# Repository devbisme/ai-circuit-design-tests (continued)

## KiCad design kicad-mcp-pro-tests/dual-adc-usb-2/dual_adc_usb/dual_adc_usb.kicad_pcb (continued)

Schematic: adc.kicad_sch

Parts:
C401, C402, C403, C404, C406, C407, C409, C410, C412, C413, C416, C417: 100n; C_0603_1608Metric
C405: 10u; C_0805_2012Metric
C408, C411, C414, C415: 2.2u; C_0603_1608Metric
R401: 20k; R_0603_1608Metric
R402: 10k; R_0603_1608Metric
R403, R404, R405, R406: 33; R_0603_1608Metric
RN401, RN402, RN403, RN404, RN405, RN406: 4x33; R_Array_Convex_4x0603
U401: LTC2290CUP; QFN-64-1EP_9x9mm_P0.5mm_EP7.15x7.15mm
U402: 74LVC1G34; SOT-23-5
X401: ASE-10.000MHz; Oscillator_SMD_Abracon_ASE-4Pin_3.2x2.5mm

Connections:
+3.3VA: C401.1, C402.1, C403.1, C404.1, C405.1, C416.1, R401.1, U401.7 (VDD), U401.10 (VDD), U401.18 (VDD), U401.19 (SENSEB), U401.21 (MUX), U401.62 (SENSEA), U401.63 (VDD), X401.1 (EN), X401.4 (Vdd); also elsewhere on the board
+3V3: C406.1, C407.1, C417.1, U401.32 (OVDD), U401.49 (OVDD), U402.5 (VCC); also elsewhere on the board
/ADC/ADC_CLK: R403.2, U401.8 (CLKA), U401.9 (CLKB)
/ADC/CLK_BUF: R404.1, U402.4
/ADC/DA0_S: RN401.1 (R1.1), U401.43 (DA0)
/ADC/DA1_S: RN401.2 (R2.1), U401.44 (DA1)
/ADC/DA2_S: RN401.3 (R3.1), U401.45 (DA2)
/ADC/DA3_S: RN401.4 (R4.1), U401.46 (DA3)
/ADC/DA4_S: RN402.1 (R1.1), U401.47 (DA4)
/ADC/DA5_S: RN402.2 (R2.1), U401.48 (DA5)
/ADC/DA6_S: RN402.3 (R3.1), U401.51 (DA6)
/ADC/DA7_S: RN402.4 (R4.1), U401.52 (DA7)
/ADC/DA8_S: RN403.1 (R1.1), U401.53 (DA8)
/ADC/DA9_S: RN403.2 (R2.1), U401.54 (DA9)
/ADC/DA10_S: RN403.3 (R3.1), U401.55 (DA10)
/ADC/DA11_S: RN403.4 (R4.1), U401.56 (DA11)
/ADC/DB0_S: RN404.1 (R1.1), U401.26 (DB0)
/ADC/DB1_S: RN404.2 (R2.1), U401.27 (DB1)
/ADC/DB2_S: RN404.3 (R3.1), U401.28 (DB2)
/ADC/DB3_S: RN404.4 (R4.1), U401.29 (DB3)
/ADC/DB4_S: RN405.1 (R1.1), U401.30 (DB4)
/ADC/DB5_S: RN405.2 (R2.1), U401.33 (DB5)
/ADC/DB6_S: RN405.3 (R3.1), U401.34 (DB6)
/ADC/DB7_S: RN405.4 (R4.1), U401.35 (DB7)
/ADC/DB8_S: RN406.1 (R1.1), U401.36 (DB8)
/ADC/DB9_S: RN406.2 (R2.1), U401.37 (DB9)
/ADC/DB10_S: RN406.3 (R3.1), U401.38 (DB10)
/ADC/DB11_S: RN406.4 (R4.1), U401.39 (DB11)
/ADC/MODE: R401.2, R402.1, U401.60 (MODE)
/ADC/OFA_S: R405.1, U401.57 (OFA)
/ADC/OFB_S: R406.1, U401.40 (OFB)
/ADC/OSC10: R403.1, U402.2, X401.3 (OUT)
/ADC/REFHA: C408.1, C409.1, U401.3 (REFHA), U401.4 (REFHA)
/ADC/REFHB: C411.1, C412.1, U401.13 (REFHB), U401.14 (REFHB)
/ADC/REFLA: C408.2, C410.1, U401.5 (REFLA), U401.6 (REFLA)
/ADC/REFLB: C411.2, C413.1, U401.11 (REFLB), U401.12 (REFLB)
ADC_CLK_FPGA: R404.2; also elsewhere on the board
AINA_N: U401.2 (AINA-); also elsewhere on the board
AINA_P: U401.1 (AINA+); also elsewhere on the board
AINB_N: U401.15 (AINB-); also elsewhere on the board
AINB_P: U401.16 (AINB+); also elsewhere on the board
DA0: RN401.8 (R1.2); also elsewhere on the board
DA1: RN401.7 (R2.2); also elsewhere on the board
DA2: RN401.6 (R3.2); also elsewhere on the board
DA3: RN401.5 (R4.2); also elsewhere on the board
DA4: RN402.8 (R1.2); also elsewhere on the board
DA5: RN402.7 (R2.2); also elsewhere on the board
DA6: RN402.6 (R3.2); also elsewhere on the board
DA7: RN402.5 (R4.2); also elsewhere on the board
DA8: RN403.8 (R1.2); also elsewhere on the board
DA9: RN403.7 (R2.2); also elsewhere on the board
DA10: RN403.6 (R3.2); also elsewhere on the board
DA11: RN403.5 (R4.2); also elsewhere on the board
DB0: RN404.8 (R1.2); also elsewhere on the board
DB1: RN404.7 (R2.2); also elsewhere on the board
DB2: RN404.6 (R3.2); also elsewhere on the board
DB3: RN404.5 (R4.2); also elsewhere on the board
DB4: RN405.8 (R1.2); also elsewhere on the board
DB5: RN405.7 (R2.2); also elsewhere on the board
DB6: RN405.6 (R3.2); also elsewhere on the board
DB7: RN405.5 (R4.2); also elsewhere on the board
DB8: RN406.8 (R1.2); also elsewhere on the board
DB9: RN406.7 (R2.2); also elsewhere on the board
DB10: RN406.6 (R3.2); also elsewhere on the board
DB11: RN406.5 (R4.2); also elsewhere on the board
GND: C401.2, C402.2, C403.2, C404.2, C405.2, C406.2, C407.2, C409.2, C410.2, C412.2, C413.2, C414.2, C415.2, C416.2, C417.2, R402.2, U401.17 (GND), U401.22 (SHDNB), U401.23 (~OEB), U401.31 (OGND), U401.50 (OGND), U401.58 (~OEA), U401.59 (SHDNA), U401.64 (GND), U401.65 (GND), U402.3 (GND), X401.2 (GND); also elsewhere on the board
OFA: R405.2; also elsewhere on the board
OFB: R406.2; also elsewhere on the board
VCMA: C414.1, U401.61 (VCMA); also elsewhere on the board
VCMB: C415.1, U401.20 (VCMB); also elsewhere on the board

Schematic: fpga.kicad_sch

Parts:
C501, C503, C509, C518: 10u; C_0805_2012Metric
C502, C504, C505, C506, C507, C508, C510, C511, C512, C513, C514, C515, C516, C517, C519, C520, C521, C522: 100n; C_0603_1608Metric
D501: GRN; LED_0603_1608Metric
D502: YEL; LED_0603_1608Metric
J501: GPIO; PinHeader_2x05_P2.54mm_Vertical
R501, R502, R503: 10k; R_0603_1608Metric
R504, R505: 100; R_0603_1608Metric
R506: 33; R_0603_1608Metric
R507, R508: 330; R_0603_1608Metric
U501: ICE40HX4K-TQ144; TQFP-144_20x20mm_P0.5mm
U502: W25Q32JVSS; SOIC-8_5.3x5.3mm_P1.27mm
X501: ASE-50.000MHz; Oscillator_SMD_Abracon_ASE-4Pin_3.2x2.5mm

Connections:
+1V2: C505.1, C506.1, C507.1, C508.1, C509.1, R504.1, R505.1, U501.27 (VCC), U501.40 (VCC), U501.92 (VCC), U501.111 (VCC); also elsewhere on the board
+3V3: C510.1, C511.1, C512.1, C513.1, C514.1, C515.1, C516.1, C517.1, C518.1, C519.1, C520.1, C521.1, C522.1, J501.9, R501.2, R502.2, R503.2, U501.6 (VCCIO_3), U501.30 (VCCIO_3), U501.46 (VCCIO_2), U501.57 (VCCIO_2), U501.72 (VCC_SPI), U501.89 (VCCIO_1), U501.100 (VCCIO_1), U501.108 (VPP_2V5), U501.123 (VCCIO_0), U501.131 (VCCIO_0), U502.3 (~WP/IO_{2}), U502.7 (~HOLD/~RESET/IO_{3}), U502.8 (VCC), X501.1 (EN), X501.4 (Vdd); also elsewhere on the board
/FPGA/GPIO0: J501.1, U501.136 (IOT_214)
/FPGA/GPIO1: J501.2, U501.137 (IOT_215)
/FPGA/GPIO2: J501.3, U501.138 (IOT_216)
/FPGA/GPIO3: J501.4, U501.139 (IOT_217)
/FPGA/GPIO4: J501.5, U501.141 (IOT_219)
/FPGA/GPIO5: J501.6, U501.142 (IOT_220)
/FPGA/GPIO6: J501.7, U501.143 (IOT_221)
/FPGA/GPIO7: J501.8, U501.144 (IOT_222)
/FPGA/LED1_A: D501.2 (A), R507.2
/FPGA/LED1_R: R507.1, U501.134 (IOT_212)
/FPGA/LED2_A: D502.2 (A), R508.2
/FPGA/LED2_R: R508.1, U501.135 (IOT_213)
/FPGA/OSC50: R506.1, X501.3 (OUT)
/FPGA/SYS_CLK: R506.2, U501.129 (IOT_198_GBIN0)
/FPGA/VCCPLL0: C501.1, C502.1, R504.2, U501.54 (VCCPLL0)
/FPGA/VCCPLL1: C503.1, C504.1, R505.2, U501.126 (VCCPLL1)
ADC_CLK_FPGA: U501.20 (IOL_13B_GBIN7); also elsewhere on the board
CDONE: R502.1, U501.65 (CDONE); also elsewhere on the board
CRESET_N: R501.1, U501.66 (~CRESET); also elsewhere on the board
DA0: U501.1 (IOL_2A); also elsewhere on the board
DA1: U501.2 (IOL_2B); also elsewhere on the board
DA2: U501.3 (IOL_3A); also elsewhere on the board
DA3: U501.4 (IOL_3B); also elsewhere on the board
DA4: U501.7 (IOL_4A); also elsewhere on the board
DA5: U501.8 (IOL_4B); also elsewhere on the board
DA6: U501.9 (IOL_5A); also elsewhere on the board
DA7: U501.10 (IOL_5B); also elsewhere on the board
DA8: U501.11 (IOL_8A); also elsewhere on the board
DA9: U501.12 (IOL_8B); also elsewhere on the board
DA10: U501.15 (IOL_10A); also elsewhere on the board
DA11: U501.16 (IOL_10B); also elsewhere on the board
DB0: U501.19 (IOL_13A); also elsewhere on the board
DB1: U501.21 (IOL_14A_GBIN6); also elsewhere on the board
DB2: U501.22 (IOL_14B); also elsewhere on the board
DB3: U501.23 (IOL_17A); also elsewhere on the board
DB4: U501.24 (IOL_17B); also elsewhere on the board
DB5: U501.25 (IOL_18A); also elsewhere on the board
DB6: U501.26 (IOL_18B); also elsewhere on the board
DB7: U501.28 (IOL_23A); also elsewhere on the board
DB8: U501.29 (IOL_23B); also elsewhere on the board
DB9: U501.31 (IOL_24A); also elsewhere on the board
DB10: U501.32 (IOL_24B); also elsewhere on the board
DB11: U501.33 (IOL_25A); also elsewhere on the board
FLASH_MISO: U501.68 (IOB_106_SDI), U502.2 (DO/IO_{1}); also elsewhere on the board
FLASH_MOSI: U501.67 (IOB_105_SDO), U502.5 (DI/IO_{0}); also elsewhere on the board
FLASH_SCK: U501.70 (IOB_107_SCK), U502.6 (CLK); also elsewhere on the board
FLASH_SS: R503.1, U501.71 (IOB_108_SS), U502.1 (~CS); also elsewhere on the board
FT_CLKOUT: U501.128 (IOT_197_GBIN1); also elsewhere on the board
FT_D0: U501.110 (IOT_168); also elsewhere on the board
FT_D1: U501.112 (IOT_169); also elsewhere on the board
FT_D2: U501.113 (IOT_170); also elsewhere on the board
FT_D3: U501.114 (IOT_171); also elsewhere on the board
FT_D4: U501.115 (IOT_172); also elsewhere on the board
FT_D5: U501.116 (IOT_173); also elsewhere on the board
FT_D6: U501.117 (IOT_174); also elsewhere on the board
FT_D7: U501.118 (IOT_177); also elsewhere on the board
FT_OE_N: U501.125 (IOT_192); also elsewhere on the board
FT_RD_N: U501.121 (IOT_181); also elsewhere on the board
FT_RXF_N: U501.119 (IOT_178); also elsewhere on the board
FT_SIWU: U501.124 (IOT_191); also elsewhere on the board
FT_TXE_N: U501.120 (IOT_179); also elsewhere on the board
FT_WR_N: U501.122 (IOT_190); also elsewhere on the board
GND: C501.2, C502.2, C503.2, C504.2, C505.2, C506.2, C507.2, C508.2, C509.2, C510.2, C511.2, C512.2, C513.2, C514.2, C515.2, C516.2, C517.2, C518.2, C519.2, C520.2, C521.2, C522.2, D501.1 (K), D502.1 (K), J501.10, U501.5 (GND), U501.13 (GND), U501.14 (GND), U501.53 (GNDPLL0), U501.59 (GND), U501.69 (GND), U501.86 (GND), U501.103 (GND), U501.127 (GNDPLL1), U501.132 (GND), U501.140 (GND), U502.4 (GND), X501.2 (GND); also elsewhere on the board
OFA: U501.17 (IOL_12A); also elsewhere on the board
OFB: U501.18 (IOL_12B); also elsewhere on the board
SD_A0: U501.37 (IOB_56); also elsewhere on the board
SD_A1: U501.38 (IOB_57); also elsewhere on the board
SD_A2: U501.39 (IOB_61); also elsewhere on the board
SD_A3: U501.41 (IOB_63); also elsewhere on the board
SD_A4: U501.42 (IOB_64); also elsewhere on the board
SD_A5: U501.43 (IOB_71); also elsewhere on the board
SD_A6: U501.44 (IOB_72); also elsewhere on the board
SD_A7: U501.45 (IOB_73); also elsewhere on the board
SD_A8: U501.47 (IOB_79); also elsewhere on the board
SD_A9: U501.48 (IOB_80); also elsewhere on the board
SD_A10: U501.55 (IOB_91); also elsewhere on the board
SD_A11: U501.56 (IOB_94); also elsewhere on the board
SD_BA0: U501.49 (IOB_81_GBIN5); also elsewhere on the board
SD_BA1: U501.52 (IOB_82_GBIN4); also elsewhere on the board
SD_CAS_N: U501.64 (IOB_104_CBSEL1); also elsewhere on the board
SD_CKE: U501.61 (IOB_96); also elsewhere on the board
SD_CLK: U501.60 (IOB_95); also elsewhere on the board
SD_CS_N: U501.62 (IOB_102); also elsewhere on the board
SD_DQ0: U501.76 (IOR_112); also elsewhere on the board
SD_DQ1: U501.78 (IOR_114); also elsewhere on the board
SD_DQ2: U501.79 (IOR_115); also elsewhere on the board
SD_DQ3: U501.80 (IOR_116); also elsewhere on the board
SD_DQ4: U501.81 (IOR_117); also elsewhere on the board
SD_DQ5: U501.82 (IOR_118); also elsewhere on the board
SD_DQ6: U501.83 (IOR_119); also elsewhere on the board
SD_DQ7: U501.84 (IOR_120); also elsewhere on the board
SD_DQ8: U501.85 (IOR_128); also elsewhere on the board
SD_DQ9: U501.87 (IOR_136); also elsewhere on the board
SD_DQ10: U501.88 (IOR_137); also elsewhere on the board
SD_DQ11: U501.90 (IOR_138); also elsewhere on the board
SD_DQ12: U501.91 (IOR_139); also elsewhere on the board
SD_DQ13: U501.95 (IOR_144); also elsewhere on the board
SD_DQ14: U501.96 (IOR_146); also elsewhere on the board
SD_DQ15: U501.97 (IOR_147); also elsewhere on the board
SD_LDQM: U501.74 (IOR_110); also elsewhere on the board
SD_RAS_N: U501.63 (IOB_103_CBSEL0); also elsewhere on the board
SD_UDQM: U501.75 (IOR_111); also elsewhere on the board
SD_WE_N: U501.73 (IOR_109); also elsewhere on the board

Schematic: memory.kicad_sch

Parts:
C601, C602, C603, C604, C605, C606, C607: 100n; C_0603_1608Metric
C608: 10u; C_0805_2012Metric
R601: 22; R_0603_1608Metric
U601: AS4C4M16SA-6TCN; TSOP-II-54_22.2x10.16mm_P0.8mm

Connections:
+3V3: C601.1, C602.1, C603.1, C604.1, C605.1, C606.1, C607.1, C608.1, U601.1 (VDD), U601.3 (VDDQ), U601.9 (VDDQ), U601.14 (VDD), U601.27 (VDD), U601.43 (VDDQ), U601.49 (VDDQ); also elsewhere on the board
/Memory/SD_CLK_R: R601.2, U601.38 (CLK)
GND: C601.2, C602.2, C603.2, C604.2, C605.2, C606.2, C607.2, C608.2, U601.6 (VSSQ), U601.12 (VSSQ), U601.28 (VSS), U601.41 (VSS), U601.46 (VSSQ), U601.52 (VSSQ), U601.54 (VSS); also elsewhere on the board
SD_A0: U601.23 (A0); also elsewhere on the board
SD_A1: U601.24 (A1); also elsewhere on the board
SD_A2: U601.25 (A2); also elsewhere on the board
SD_A3: U601.26 (A3); also elsewhere on the board
SD_A4: U601.29 (A4); also elsewhere on the board
SD_A5: U601.30 (A5); also elsewhere on the board
SD_A6: U601.31 (A6); also elsewhere on the board
SD_A7: U601.32 (A7); also elsewhere on the board
SD_A8: U601.33 (A8); also elsewhere on the board
SD_A9: U601.34 (A9); also elsewhere on the board
SD_A10: U601.22 (A10/AP); also elsewhere on the board
SD_A11: U601.35 (A11); also elsewhere on the board
SD_BA0: U601.20 (BA0); also elsewhere on the board
SD_BA1: U601.21 (BA1); also elsewhere on the board
SD_CAS_N: U601.17 (~CAS); also elsewhere on the board
SD_CKE: U601.37 (CKE); also elsewhere on the board
SD_CLK: R601.1; also elsewhere on the board
SD_CS_N: U601.19 (~CS); also elsewhere on the board
SD_DQ0: U601.2 (DQ0); also elsewhere on the board
SD_DQ1: U601.4 (DQ1); also elsewhere on the board
SD_DQ2: U601.5 (DQ2); also elsewhere on the board
SD_DQ3: U601.7 (DQ3); also elsewhere on the board
SD_DQ4: U601.8 (DQ4); also elsewhere on the board
SD_DQ5: U601.10 (DQ5); also elsewhere on the board
SD_DQ6: U601.11 (DQ6); also elsewhere on the board
SD_DQ7: U601.13 (DQ7); also elsewhere on the board
SD_DQ8: U601.42 (DQ8); also elsewhere on the board
SD_DQ9: U601.44 (DQ9); also elsewhere on the board
SD_DQ10: U601.45 (DQ10); also elsewhere on the board
SD_DQ11: U601.47 (DQ11); also elsewhere on the board
SD_DQ12: U601.48 (DQ12); also elsewhere on the board
SD_DQ13: U601.50 (DQ13); also elsewhere on the board
SD_DQ14: U601.51 (DQ14); also elsewhere on the board
SD_DQ15: U601.53 (DQ15); also elsewhere on the board
SD_LDQM: U601.15 (LDQM); also elsewhere on the board
SD_RAS_N: U601.18 (~RAS); also elsewhere on the board
SD_UDQM: U601.39 (UDQM); also elsewhere on the board
SD_WE_N: U601.16 (~WE); also elsewhere on the board

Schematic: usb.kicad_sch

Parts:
C701: 10u; C_0805_2012Metric
C702, C706, C707, C709, C710, C711, C712, C713, C714, C715, C717, C718: 100n; C_0603_1608Metric
C703, C704: 18p; C_0603_1608Metric
C705, C708, C716: 4.7u; C_0603_1608Metric
F701: 500mA; Fuse_1206_3216Metric
FB701: 600R@100MHz; L_0805_2012Metric
FB702: 600R@100MHz; L_0603_1608Metric
J701: USB_B; USB_B_OST_USB-B1HSxx_Horizontal
R701: 12k 1%; R_0603_1608Metric
R702, R704: 10k; R_0603_1608Metric
R703: 2.2k; R_0603_1608Metric
U701: USBLC6-2SC6; SOT-23-6
U702: FT2232HL; LQFP-64_10x10mm_P0.5mm
U703: 93LC56B; SOIC-8_3.9x4.9mm_P1.27mm
Y701: 12MHz; Crystal_SMD_3225-4Pin_3.2x2.5mm

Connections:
+3V3: C712.1, C713.1, C714.1, C715.1, C716.1, C717.1, C718.1, FB702.1, R702.2, R704.2, U702.20 (VCCIO), U702.31 (VCCIO), U702.42 (VCCIO), U702.50 (VREGIN), U702.56 (VCCIO), U703.8 (VCC); also elsewhere on the board
+5V: C701.1, FB701.2; also elsewhere on the board
/USB/EECLK: U702.62 (EECLK), U703.2 (SCLK)
/USB/EECS: U702.63 (EECS), U703.1 (CS)
/USB/EEDATA: R703.1, R704.1, U702.61 (EEDATA), U703.3 (DI)
/USB/EE_DO: R703.2, U703.4 (DO)
/USB/FT_REF: R701.1, U702.6 (REF)
/USB/FT_RST_N: R702.1, U702.14 (~RESET)
/USB/USB_DM: J701.2 (D-), U701.1 (I/O1), U701.6 (I/O1), U702.7 (DM)
/USB/USB_DP: J701.3 (D+), U701.3 (I/O2), U701.4 (I/O2), U702.8 (DP)
/USB/VBUS_F: C702.1, F701.2, FB701.1, U701.5 (VBUS)
/USB/VCORE: C708.1, C709.1, C710.1, C711.1, U702.12 (VCORE), U702.37 (VCORE), U702.49 (VREGOUT), U702.64 (VCORE)
/USB/VPLL_PHY: C705.1, C706.1, C707.1, FB702.2, U702.4 (VPHY), U702.9 (VPLL)
/USB/XTAL_I: C703.1, U702.2 (OSCI), Y701.1
/USB/XTAL_O: C704.1, U702.3 (OSCO), Y701.3
CDONE: U702.45 (BDBUS6); also elsewhere on the board
CRESET_N: U702.46 (BDBUS7); also elsewhere on the board
FLASH_MISO: U702.40 (BDBUS2); also elsewhere on the board
FLASH_MOSI: U702.39 (BDBUS1); also elsewhere on the board
FLASH_SCK: U702.38 (BDBUS0); also elsewhere on the board
FLASH_SS: U702.43 (BDBUS4); also elsewhere on the board
FT_CLKOUT: U702.32 (ACBUS5); also elsewhere on the board
FT_D0: U702.16 (ADBUS0); also elsewhere on the board
FT_D1: U702.17 (ADBUS1); also elsewhere on the board
FT_D2: U702.18 (ADBUS2); also elsewhere on the board
FT_D3: U702.19 (ADBUS3); also elsewhere on the board
FT_D4: U702.21 (ADBUS4); also elsewhere on the board
FT_D5: U702.22 (ADBUS5); also elsewhere on the board
FT_D6: U702.23 (ADBUS6); also elsewhere on the board
FT_D7: U702.24 (ADBUS7); also elsewhere on the board
FT_OE_N: U702.33 (ACBUS6); also elsewhere on the board
FT_RD_N: U702.28 (ACBUS2); also elsewhere on the board
FT_RXF_N: U702.26 (ACBUS0); also elsewhere on the board
FT_SIWU: U702.30 (ACBUS4); also elsewhere on the board
FT_TXE_N: U702.27 (ACBUS1); also elsewhere on the board
FT_WR_N: U702.29 (ACBUS3); also elsewhere on the board
GND: C701.2, C702.2, C703.2, C704.2, C705.2, C706.2, C707.2, C708.2, C709.2, C710.2, C711.2, C712.2, C713.2, C714.2, C715.2, C716.2, C717.2, C718.2, J701.4 (GND), J701.SH (Shield), R701.2, U701.2 (GND), U702.1 (GND), U702.5 (GND), U702.10 (AGND), U702.11 (GND), U702.13 (TEST), U702.15 (GND), U702.25 (GND), U702.35 (GND), U702.47 (GND), U702.51 (GND), U703.5 (GND), Y701.2 (G), Y701.4 (G); also elsewhere on the board
VBUS: F701.1, J701.1 (VBUS)

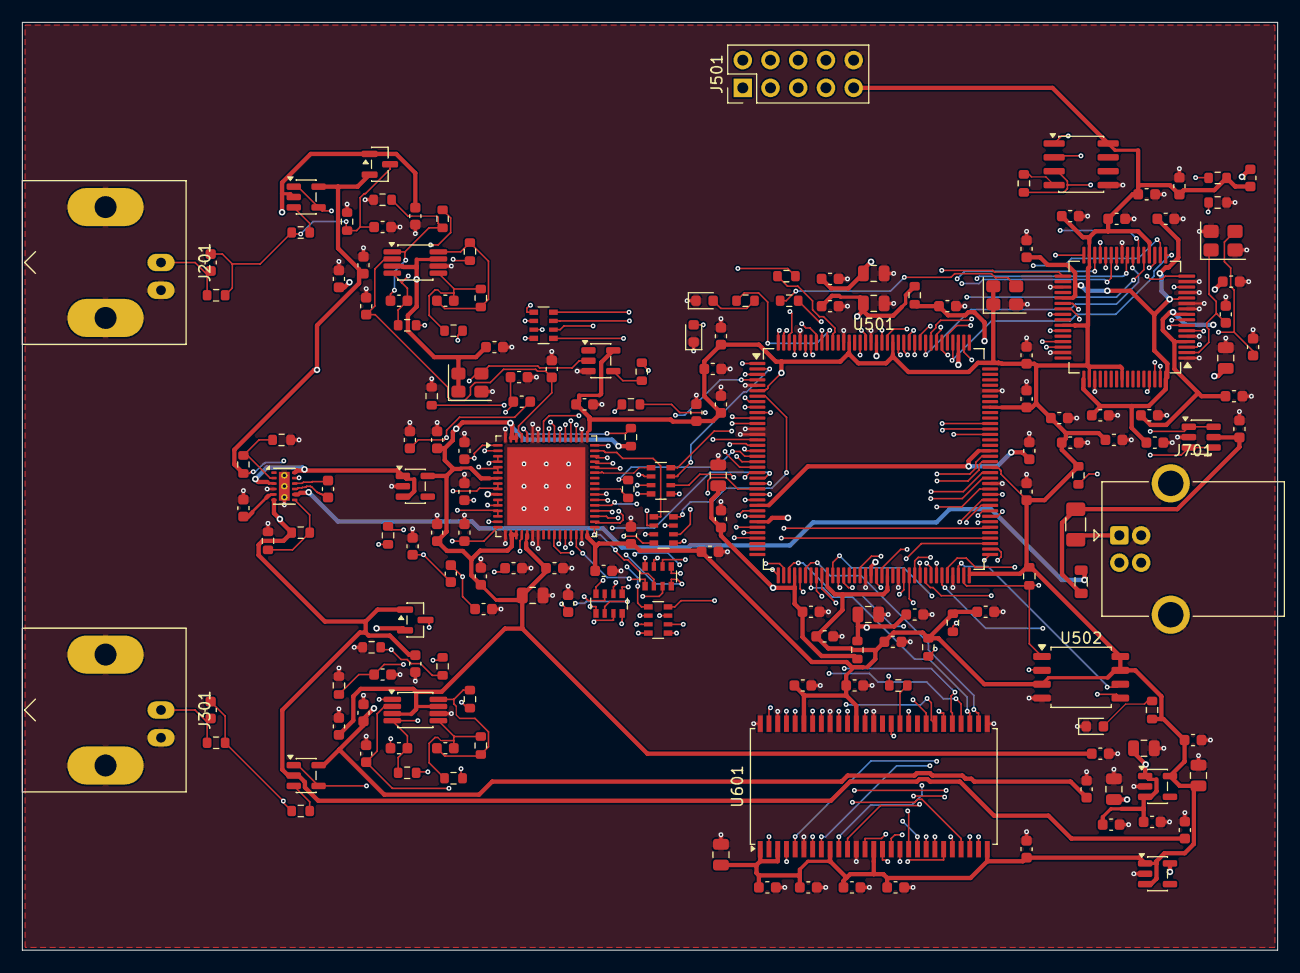
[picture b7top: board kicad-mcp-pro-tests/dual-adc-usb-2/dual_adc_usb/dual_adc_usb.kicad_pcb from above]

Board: 4 copper layers, 115.0 x 85.0 mm, 175 parts (0 on the bottom side), 186 nets.

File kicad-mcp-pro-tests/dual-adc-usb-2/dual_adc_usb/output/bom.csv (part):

reference,value,footprint,lib_id,lcsc,mpn,manufacturer,populate
C412,100n,Capacitor_SMD:C_0603_1608Metric,Device:C,,,,Populate
C416,100n,Capacitor_SMD:C_0603_1608Metric,Device:C,,,,Populate
RN403,4x33,Resistor_SMD:R_Array_Convex_4x0603,Device:R_Pack04,,,,Populate
RN404,4x33,Resistor_SMD:R_Array_Convex_4x0603,Device:R_Pack04,,,,Populate
C409,100n,Capacitor_SMD:C_0603_1608Metric,Device:C,,,,Populate
R404,33,Resistor_SMD:R_0603_1608Metric,Device:R,,,,Populate
C404,100n,Capacitor_SMD:C_0603_1608Metric,Device:C,,,,Populate
C403,100n,Capacitor_SMD:C_0603_1608Metric,Device:C,,,,Populate
R401,20k,Resistor_SMD:R_0603_1608Metric,Device:R,,,,Populate
RN406,4x33,Resistor_SMD:R_Array_Convex_4x0603,Device:R_Pack04,,,,Populate
C405,10u,Capacitor_SMD:C_0805_2012Metric,Device:C,,,,Populate
RN401,4x33,Resistor_SMD:R_Array_Convex_4x0603,Device:R_Pack04,,,,Populate
R405,33,Resistor_SMD:R_0603_1608Metric,Device:R,,,,Populate
C411,2.2u,Capacitor_SMD:C_0603_1608Metric,Device:C,,,,Populate
C406,100n,Capacitor_SMD:C_0603_1608Metric,Device:C,,,,Populate
C402,100n,Capacitor_SMD:C_0603_1608Metric,Device:C,,,,Populate
R402,10k,Resistor_SMD:R_0603_1608Metric,Device:R,,,,Populate
C410,100n,Capacitor_SMD:C_0603_1608Metric,Device:C,,,,Populate
RN405,4x33,Resistor_SMD:R_Array_Convex_4x0603,Device:R_Pack04,,,,Populate
C408,2.2u,Capacitor_SMD:C_0603_1608Metric,Device:C,,,,Populate
C414,2.2u,Capacitor_SMD:C_0603_1608Metric,Device:C,,,,Populate
U402,74LVC1G34,Package_TO_SOT_SMD:SOT-23-5,74xGxx:74LVC1G34,,,,Populate
C417,100n,Capacitor_SMD:C_0603_1608Metric,Device:C,,,,Populate
C401,100n,Capacitor_SMD:C_0603_1608Metric,Device:C,,,,Populate
RN402,4x33,Resistor_SMD:R_Array_Convex_4x0603,Device:R_Pack04,,,,Populate
R406,33,Resistor_SMD:R_0603_1608Metric,Device:R,,,,Populate
C415,2.2u,Capacitor_SMD:C_0603_1608Metric,Device:C,,,,Populate
U401,LTC2290CUP,Package_DFN_QFN:QFN-64-1EP_9x9mm_P0.5mm_EP7.15x7.15mm,Analog_ADC:LTC2290xUP,,,,Populate
C413,100n,Capacitor_SMD:C_0603_1608Metric,Device:C,,,,Populate
X401,ASE-10.000MHz,Oscillator:Oscillator_SMD_Abracon_ASE-4Pin_3.2x2.5mm,Oscillator:ASE-xxxMHz,,,,Populate
R403,33,Resistor_SMD:R_0603_1608Metric,Device:R,,,,Populate
C407,100n,Capacitor_SMD:C_0603_1608Metric,Device:C,,,,Populate
C205,33p C0G,Capacitor_SMD:C_0603_1608Metric,Device:C,,,,Populate
C202,160p C0G,Capacitor_SMD:C_0603_1608Metric,Device:C,,,,Populate
C201,18p C0G,Capacitor_SMD:C_0603_1608Metric,Device:C,,,,Populate
R208,49.9,Resistor_SMD:R_0603_1608Metric,Device:R,,,,Populate
R203,1k,Resistor_SMD:R_0603_1608Metric,Device:R,,,,Populate
U201,OPA810IDBV,Package_TO_SOT_SMD:SOT-23-5,Amplifier_Operational:OPA810xDBV,,,,Populate
R205,1.1k 0.1%,Resistor_SMD:R_0603_1608Metric,Device:R,,,,Populate
C208,100n,Capacitor_SMD:C_0603_1608Metric,Device:C,,,,Populate
U202,THS4521IDGK,Package_SO:VSSOP-8_3x3mm_P0.65mm,Amplifier_Difference:THS4521IDGK,,,,Populate
C204,100n,Capacitor_SMD:C_0603_1608Metric,Device:C,,,,Populate
D201,BAV99,Package_TO_SOT_SMD:SOT-23,Diode:BAV99,,,,Populate
C203,100n,Capacitor_SMD:C_0603_1608Metric,Device:C,,,,Populate
C207,100n,Capacitor_SMD:C_0603_1608Metric,Device:C,,,,Populate
C209,33p C0G,Capacitor_SMD:C_0603_1608Metric,Device:C,,,,Populate
C210,33p C0G,Capacitor_SMD:C_0603_1608Metric,Device:C,,,,Populate
C206,33p C0G,Capacitor_SMD:C_0603_1608Metric,Device:C,,,,Populate
R202,101k 0.1%,Resistor_SMD:R_0603_1608Metric,Device:R,,,,Populate
R209,49.9,Resistor_SMD:R_0603_1608Metric,Device:R,,,,Populate
R206,1.0k 0.1%,Resistor_SMD:R_0603_1608Metric,Device:R,,,,Populate
J201,BNC CH_A,Connector_Coaxial:BNC_Amphenol_B6252HB-NPP3G-50_Horizontal,Connector:Conn_Coaxial,,,,Populate
R207,1.0k 0.1%,Resistor_SMD:R_0603_1608Metric,Device:R,,,,Populate
R204,1.1k 0.1%,Resistor_SMD:R_0603_1608Metric,Device:R,,,,Populate
R201,909k 0.1%,Resistor_SMD:R_0603_1608Metric,Device:R,,,,Populate
R303,1k,Resistor_SMD:R_0603_1608Metric,Device:R,,,,Populate
D301,BAV99,Package_TO_SOT_SMD:SOT-23,Diode:BAV99,,,,Populate
U302,THS4521IDGK,Package_SO:VSSOP-8_3x3mm_P0.65mm,Amplifier_Difference:THS4521IDGK,,,,Populate
C303,100n,Capacitor_SMD:C_0603_1608Metric,Device:C,,,,Populate
R307,1.0k 0.1%,Resistor_SMD:R_0603_1608Metric,Device:R,,,,Populate
J301,BNC CH_B,Connector_Coaxial:BNC_Amphenol_B6252HB-NPP3G-50_Horizontal,Connector:Conn_Coaxial,,,,Populate
C301,18p C0G,Capacitor_SMD:C_0603_1608Metric,Device:C,,,,Populate
R306,1.0k 0.1%,Resistor_SMD:R_0603_1608Metric,Device:R,,,,Populate
R309,49.9,Resistor_SMD:R_0603_1608Metric,Device:R,,,,Populate
R308,49.9,Resistor_SMD:R_0603_1608Metric,Device:R,,,,Populate
C309,33p C0G,Capacitor_SMD:C_0603_1608Metric,Device:C,,,,Populate
C304,100n,Capacitor_SMD:C_0603_1608Metric,Device:C,,,,Populate
C310,33p C0G,Capacitor_SMD:C_0603_1608Metric,Device:C,,,,Populate
R305,1.1k 0.1%,Resistor_SMD:R_0603_1608Metric,Device:R,,,,Populate
C307,100n,Capacitor_SMD:C_0603_1608Metric,Device:C,,,,Populate
C308,100n,Capacitor_SMD:C_0603_1608Metric,Device:C,,,,Populate
C302,160p C0G,Capacitor_SMD:C_0603_1608Metric,Device:C,,,,Populate
C306,33p C0G,Capacitor_SMD:C_0603_1608Metric,Device:C,,,,Populate
U301,OPA810IDBV,Package_TO_SOT_SMD:SOT-23-5,Amplifier_Operational:OPA810xDBV,,,,Populate
R304,1.1k 0.1%,Resistor_SMD:R_0603_1608Metric,Device:R,,,,Populate
C305,33p C0G,Capacitor_SMD:C_0603_1608Metric,Device:C,,,,Populate
R301,909k 0.1%,Resistor_SMD:R_0603_1608Metric,Device:R,,,,Populate
R302,101k 0.1%,Resistor_SMD:R_0603_1608Metric,Device:R,,,,Populate
U501,ICE40HX4K-TQ144,Package_QFP:TQFP-144_20x20mm_P0.5mm,FPGA_Lattice:ICE40HX4K-TQ144,,,,Populate
R503,10k,Resistor_SMD:R_0603_1608Metric,Device:R,,,,Populate
C516,100n,Capacitor_SMD:C_0603_1608Metric,Device:C,,,,Populate
R506,33,Resistor_SMD:R_0603_1608Metric,Device:R,,,,Populate
C519,100n,Capacitor_SMD:C_0603_1608Metric,Device:C,,,,Populate
C508,100n,Capacitor_SMD:C_0603_1608Metric,Device:C,,,,Populate
C502,100n,Capacitor_SMD:C_0603_1608Metric,Device:C,,,,Populate
C520,100n,Capacitor_SMD:C_0603_1608Metric,Device:C,,,,Populate
C503,10u,Capacitor_SMD:C_0805_2012Metric,Device:C,,,,Populate
D502,YEL,LED_SMD:LED_0603_1608Metric,Device:LED,,,,Populate
R505,100,Resistor_SMD:R_0603_1608Metric,Device:R,,,,Populate
C511,100n,Capacitor_SMD:C_0603_1608Metric,Device:C,,,,Populate
C514,100n,Capacitor_SMD:C_0603_1608Metric,Device:C,,,,Populate
C517,100n,Capacitor_SMD:C_0603_1608Metric,Device:C,,,,Populate
C507,100n,Capacitor_SMD:C_0603_1608Metric,Device:C,,,,Populate
J501,GPIO,Connector_PinHeader_2.54mm:PinHeader_2x05_P2.54mm_Vertical,Connector_Generic:Conn_02x05_Odd_Even,,,,Populate
C501,10u,Capacitor_SMD:C_0805_2012Metric,Device:C,,,,Populate
C510,100n,Capacitor_SMD:C_0603_1608Metric,Device:C,,,,Populate
R501,10k,Resistor_SMD:R_0603_1608Metric,Device:R,,,,Populate
R508,330,Resistor_SMD:R_0603_1608Metric,Device:R,,,,Populate
R504,100,Resistor_SMD:R_0603_1608Metric,Device:R,,,,Populate
C504,100n,Capacitor_SMD:C_0603_1608Metric,Device:C,,,,Populate
C515,100n,Capacitor_SMD:C_0603_1608Metric,Device:C,,,,Populate
C512,100n,Capacitor_SMD:C_0603_1608Metric,Device:C,,,,Populate
C505,100n,Capacitor_SMD:C_0603_1608Metric,Device:C,,,,Populate
C518,10u,Capacitor_SMD:C_0805_2012Metric,Device:C,,,,Populate
X501,ASE-50.000MHz,Oscillator:Oscillator_SMD_Abracon_ASE-4Pin_3.2x2.5mm,Oscillator:ASE-xxxMHz,,,,Populate
D501,GRN,LED_SMD:LED_0603_1608Metric,Device:LED,,,,Populate
C506,100n,Capacitor_SMD:C_0603_1608Metric,Device:C,,,,Populate
C509,10u,Capacitor_SMD:C_0805_2012Metric,Device:C,,,,Populate
R507,330,Resistor_SMD:R_0603_1608Metric,Device:R,,,,Populate
C513,100n,Capacitor_SMD:C_0603_1608Metric,Device:C,,,,Populate
C521,100n,Capacitor_SMD:C_0603_1608Metric,Device:C,,,,Populate
U502,W25Q32JVSS,Package_SO:SOIC-8_5.3x5.3mm_P1.27mm,Memory_Flash:W25Q32JVSS,,,,Populate
R502,10k,Resistor_SMD:R_0603_1608Metric,Device:R,,,,Populate
C522,100n,Capacitor_SMD:C_0603_1608Metric,Device:C,,,,Populate
C607,100n,Capacitor_SMD:C_0603_1608Metric,Device:C,,,,Populate
C604,100n,Capacitor_SMD:C_0603_1608Metric,Device:C,,,,Populate
C603,100n,Capacitor_SMD:C_0603_1608Metric,Device:C,,,,Populate
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
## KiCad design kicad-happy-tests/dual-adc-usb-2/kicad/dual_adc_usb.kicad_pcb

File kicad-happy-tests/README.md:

# kicad-happy — tests

## Tool under test

[kicad-happy](https://github.com/aklofas/kicad-happy) is a Claude Code plugin of 11 skills
(`kicad`, `spice`, `emc`, `datasheets`, `bom`, `digikey`, `mouser`, `lcsc`, `element14`,
`jlcpcb`, `pcbway`) that review and analyze existing KiCad designs. Its scripts parse
`.kicad_sch` / `.kicad_pcb` files directly with the Python standard library. It does not
create schematics or layouts, so it is an **analyzer**, not a generator.
Installation is described in [`setup.md`](setup.md).

- **Version:** kicad-happy 2.3.1.
- **Model:** Claude Opus 5.5 on a Claude Pro plan.
- **Backend:** KiCad 10.0.4 `kicad-cli` (`/home/devb/bin/kicad10`) for ERC/DRC and zone
  refill; ngspice 44.2 for simulation.
- No distributor API keys were available, so sourcing and lifecycle checks were not run.

## Runs

The two subdirectories test kicad-happy in different roles:

| Run | Purpose | kicad-happy's role | Session |
|-----|---------|--------------------|---------|
| [`dual-adc-usb-1`](dual-adc-usb-1/) | Review an **existing** design | The whole job: analyze and report | ~7 min, 3 prompts, $1.92 |
| [`dual-adc-usb-2`](dual-adc-usb-2/) | Design a board **from scratch**, with kicad-happy installed | Review step inside a larger design flow | ~3.5 h, 2 prompts, $29.37 |

Costs are equivalent first-party API cost, not what the Pro plan billed.

### dual-adc-usb-1: analyzer on an existing design

Tests kicad-happy as advertised: point it at a finished KiCad project and see what it
finds.

- **Input:** the KiCad project produced by
  [Konnect run 2](../konnect-tests/dual-adc-usb-2/): a 4-layer, 140 × 90 mm dual-channel
  12-bit, 10 MS/s ADC board with USB 2.0 (LTC2290 ADC, iCE40HX4K FPGA, SDRAM, FT2232HL).
  The schematic files are unchanged copies of Konnect's. The `.kicad_pro` and
  `.kicad_pcb` differ because the session relaxed the design rules and refilled the zones.
- **Skills used:** `kicad`, `emc`, `spice`. No datasheets were available.
- **Claude Code:** v2.1.293.
- **Results:**
  - Found one real layout defect: the board was routed at ~0.15 mm clearance/width but its
    rules said 0.2 mm (524 DRC errors). At the user's request the rules were relaxed to
    0.15 mm and the zones refilled; DRC then showed 0 errors.
  - Flagged missing MPNs, fiducials and test points, and thin via counts under some
    exposed pads.
  - Several findings were false positives on inspection, including all 134 EMC
    ground-plane-gap findings.
  - Every finding is a self-consistency check only, since no part has an MPN or datasheet.
- **Details:** [`executive-summary.md`](dual-adc-usb-1/executive-summary.md). I have not
  yet validated its findings myself.

Prompts, in sequence in one session (from `claude_transcript.txt`):

```
use kicad-happy to analyze the kicad project in this directory. A KiCad 10
executable is in /home/devb/bin/kicad10.
```
```
relax the rules to 0.15 mm, refill and save the board
```
```
write an executive summary file explaining what you did and what results were
found for this kicad project.
```

### dual-adc-usb-2: full design with kicad-happy available

Tests whether having kicad-happy installed helps Claude produce a design from a
requirements prompt. kicad-happy cannot create schematics or layouts, so Claude built the
board with SKiDL, its own scripts, and Freerouting, then used kicad-happy to review it.
The prompt is identical to the one used in Konnect run 2 and both kicad-mcp-server runs,
and it forbids reusing outputs of other designs in the tree.

- **Input:** [`dual-adc-prompt.txt`](dual-adc-usb-2/dual-adc-prompt.txt) only.
- **Skills used:** the full analysis suite (schematic, PCB, cross-domain, EMC, thermal,
  Gerber, SPICE). Datasheets were downloaded for most parts, but not for the
  LTC2291 ADC or the FT2232H.
- **Claude Code:** v2.1.295.
- **Result (as reported by the session):** a complete KiCad 10 project. It has a
  130 × 90 mm 4-layer board (LTC2291, iCE40HX4K, 8 MB SDRAM, FT2232H, USB-B), 0 ERC
  violations, 0 DRC errors, 100 % MPN coverage, and fab outputs.
  - Open items include unverified ADC and USB-bridge pin wiring, 0.1 mm track/space on the
    ADC bus, a 2nd-order anti-alias filter, and high EMC risk.
  - SKiDL's built-in schematic generator produced a wrong schematic, so Claude wrote a
    replacement (`scripts/sch_writer.py`).
- **Details:** [`executive_summary.md`](dual-adc-usb-2/executive_summary.md),
  [`design_decisions.md`](dual-adc-usb-2/design_decisions.md),
  [`design_review.md`](dual-adc-usb-2/design_review.md), and the run's own
  [`README.md`](dual-adc-usb-2/README.md) (file map and regeneration commands). I have
  not yet validated the design myself.

Prompts, in sequence in one session (from `transcript.txt`):

```
create the design described in dual-adc-prompt.txt
```
```
create an executive_summary.md file explaining what was done.
```

## Layout

```
kicad-happy-tests/
├── README.md                   <- this file
├── setup.md                    <- how kicad-happy was installed, verified and upgraded
├── dual-adc-usb-1/             <- run 1: analysis of an existing design
│   ├── executive-summary.md    <- what was run, findings, false positives, changes made
│   ├── claude_transcript.txt   <- session transcript (/export)
│   ├── claude_cost.txt         <- token usage and equivalent API cost
│   ├── session_cost.py         <- script that produced claude_cost.txt
│   ├── dual_adc_usb.kicad_pro  <- KiCad project (rules relaxed to 0.15 mm by this run)
│   ├── dual_adc_usb.kicad_pcb  <- board (zones refilled and saved by this run)
│   ├── dual_adc_usb.kicad_prl  <- KiCad local settings
│   ├── dual_adc_usb.kicad_sch  <- root schematic
│   ├── afe_a.kicad_sch, afe_b.kicad_sch   <- analog front ends
│   ├── adc.kicad_sch, fpga.kicad_sch, usb.kicad_sch, power.kicad_sch
│   └── analysis/               <- kicad-happy output
│       ├── manifest.json       <- run index and source-file hashes
│       ├── capability_mode.json<- what was available (0 % datasheet coverage, no LLM review)
│       └── 2026-10-07_1748/    <- analyzer reports, JSON
│           ├── schematic.json, pcb.json, cross_analysis.json
│           ├── emc.json, thermal.json, spice.json, parasitics.json
│           ├── erc.json        <- KiCad ERC
│           ├── drc.json        <- KiCad DRC, as received
│           ├── drc_refill.json <- KiCad DRC after zone refill, old rules
│           └── drc_after.json  <- KiCad DRC after rule change and refill
└── dual-adc-usb-2/             <- run 2: design from scratch (file map in its README.md)
```

Notes on run 1:

- The reports in `analysis/2026-10-07_1748/` (except `drc_after.json`) describe the board
  *before* the rule change.
- `analysis/.gitignore`, written by kicad-happy, excludes everything in `analysis/` except
  `manifest.json` because the reports can be regenerated. Remove or edit it if the reports
  should be committed.

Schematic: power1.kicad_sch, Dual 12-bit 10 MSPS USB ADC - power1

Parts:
C1, C5: 100nF; C_0603_1608Metric; MPN GRM188R71C104KA01D
C2: 6.8pF; C_0603_1608Metric; MPN GRM1885C1H6R8DA01D
C3, C11: 4.7uF; C_0805_2012Metric; MPN GRM21BR71C475KE51L
C4: 22uF; C_0805_2012Metric; MPN GRM21BR61A226ME44L
C6, C9: 10uF; C_0805_2012Metric; MPN GRM21BR61C106KE15L
C7, C8, C10: 1uF; C_0603_1608Metric; MPN GRM188R71C105KA12D
C12, C13, C14: 2.2uF; C_0603_1608Metric; MPN GRM188R61C225KE15D
D1: GRN; LED_0603_1608Metric; MPN LTST-C191KGKT
F1: 500mA; Fuse_1206_3216Metric; MPN MF-MSMF050-2
FB1: 120R@100MHz 2A; L_0805_2012Metric; MPN BLM21PG121SN1D
L1: 2.2uH; L_Changjiang_FNR4020S; MPN FNR4020S2R2MT
R1: 453k; R_0603_1608Metric; Tolerance 1%; MPN RC0603FR-07453KL
R2, R3, R6, R8: 100k; R_0603_1608Metric; Tolerance 1%; MPN RC0603FR-07100KL
R4: 10k; R_0603_1608Metric; Tolerance 1%; MPN RC0603FR-0710KL
R5: 174k; R_0603_1608Metric; Tolerance 1%; MPN RC0603FR-07174KL
R7: 169k; R_0603_1608Metric; Tolerance 1%; MPN RC0603FR-07169KL
R9: 1k; R_0603_1608Metric; Tolerance 1%; MPN RC0603FR-071KL
U1: TLV62569DBV; SOT-23-5; MPN TLV62569DBVR
U2: AP2112K-1.2; SOT-23-5; MPN AP2112K-1.2TRG1
U3: LP5907MFX-3.3; SOT-23-5; MPN LP5907MFX-3.3/NOPB
U4: LM27762; WSON-12-1EP_3x2mm_P0.5mm_EP1x2.65_ThermalVias; MPN LM27762DSSR

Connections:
+1V2: C6.1, U2.5 (VOUT); also elsewhere on the board
+3V3: C2.1, C4.1, C5.1, C7.1, L1.2, R1.1, R4.1, R9.1, U2.1 (VIN), U2.3 (EN); also elsewhere on the board
+3V3A: C13.1, R5.1, U4.11 (OUT+); also elsewhere on the board
+3V3_ADC: C9.1, U3.5 (OUT); also elsewhere on the board
+5V: C1.1, C3.1, C8.1, C12.1, FB1.2, U1.1 (EN), U1.4 (VIN), U3.1 (IN), U3.3 (EN), U4.3 (VIN)
-3V3A: C14.1, R7.1, U4.6 (OUT-); also elsewhere on the board
/power1/BUCK_FB: C2.2, R1.2, R2.1, U1.5 (FB)
/power1/BUCK_SW: L1.1, U1.3 (SW)
/power1/CP_C1N: C10.2, U4.9 (C-)
/power1/CP_C1P: C10.1, U4.10 (C+)
/power1/CP_OUT: C11.1, U4.5 (CP)
/power1/LDON_FB: R7.2, R8.1, U4.7 (FB-)
/power1/LDOP_FB: R5.2, R6.1, U4.2 (FB+)
/power1/N$67: D1.2 (A), R9.2
/power1/VBUS_F: F1.2, FB1.1
ANA_EN: R3.1, U4.8 (EN-), U4.12 (EN+); also elsewhere on the board
ANA_PG_N: R4.2, U4.1 (PGOOD); also elsewhere on the board
GND: C1.2, C3.2, C4.2, C5.2, C6.2, C7.2, C8.2, C9.2, C11.2, C12.2, C13.2, C14.2, D1.1 (K), R2.2, R3.2, R6.2, R8.2, U1.2 (GND), U2.2 (GND), U3.2 (GND), U4.4 (GND), U4.13 (PAD); also elsewhere on the board
VBUS: F1.1; also elsewhere on the board

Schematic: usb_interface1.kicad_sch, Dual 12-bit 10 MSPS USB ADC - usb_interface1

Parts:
C15: 4.7nF; C_1206_3216Metric; MPN GRM31BR72J472KW01L
C16, C19, C23: 4.7uF; C_0805_2012Metric; MPN GRM21BR71C475KE51L
C17, C18, C20, C21, C22, C24, C25, C26, C27, C28, C31: 100nF; C_0603_1608Metric; MPN GRM188R71C104KA01D
C29, C30: 27pF; C_0603_1608Metric; MPN GRM1885C1H270JA01D
FB2: 600R@100MHz; L_0603_1608Metric; MPN BLM18KG601SN1D
J1: USB_B; USB_B_OST_USB-B1HSxx_Horizontal; MPN USB-B1HSW6
R10: 1M; R_0603_1608Metric; Tolerance 1%; MPN RC0603FR-071ML
R11: 12k; R_0603_1608Metric; Tolerance 1%; MPN RC0603FR-0712KL
R12, R14, R15, R16, R17, R18: 10k; R_0603_1608Metric; Tolerance 1%; MPN RC0603FR-0710KL
R13: 2.2k; R_0603_1608Metric; Tolerance 1%; MPN RC0603FR-072K2L
U5: USBLC6-2SC6; SOT-23-6; MPN USBLC6-2SC6
U6: FT2232HL; LQFP-64_10x10mm_P0.5mm; MPN FT2232HL-REEL
U7: 93LC56B; SOIC-8_3.9x4.9mm_P1.27mm; MPN 93LC56BT-I/SN
Y1: 12MHz; Crystal_SMD_3225-4Pin_3.2x2.5mm; MPN ABM8-12.000MHZ-B2-T

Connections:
+3V3: C23.1, C24.1, C25.1, C26.1, C27.1, C28.1, C31.1, FB2.1, R12.1, R14.1, R15.1, R16.1, R17.1, R18.1, U6.20 (VCCIO), U6.31 (VCCIO), U6.42 (VCCIO), U6.50 (VREGIN), U6.56 (VCCIO), U7.8 (VCC); also elsewhere on the board
/usb_interface1/FT_EECLK: R15.2, U6.62 (EECLK), U7.2 (SCLK)
/usb_interface1/FT_EECS: R14.2, U6.63 (EECS), U7.1 (CS)
/usb_interface1/FT_EEDATA: R13.1, R16.2, U6.61 (EEDATA), U7.4 (DO)
/usb_interface1/FT_OSCI: C29.1, U6.2 (OSCI), Y1.1
/usb_interface1/FT_OSCO: C30.1, U6.3 (OSCO), Y1.3
/usb_interface1/FT_VCORE: C19.1, C20.1, C21.1, C22.1, U6.12 (VCORE), U6.37 (VCORE), U6.49 (VREGOUT), U6.64 (VCORE)
/usb_interface1/FT_VPHY: C16.1, C17.1, C18.1, FB2.2, U6.4 (VPHY), U6.9 (VPLL)
/usb_interface1/N$68: R11.1, U6.6 (REF)
/usb_interface1/N$69: R12.2, U6.14 (~RESET)
/usb_interface1/N$70: R13.2, U7.3 (DI)
/usb_interface1/USB_DM: J1.2 (D-), U5.3 (I/O2), U5.4 (I/O2), U6.7 (DM)
/usb_interface1/USB_DP: J1.3 (D+), U5.1 (I/O1), U5.6 (I/O1), U6.8 (DP)
/usb_interface1/USB_SHIELD: C15.1, J1.SH (Shield), R10.1
CFG_CDONE: U6.23 (ADBUS6); also elsewhere on the board
CFG_CRESET: U6.24 (ADBUS7); also elsewhere on the board
CFG_CS: U6.21 (ADBUS4); also elsewhere on the board
CFG_MISO: U6.18 (ADBUS2); also elsewhere on the board
CFG_MOSI: U6.17 (ADBUS1); also elsewhere on the board
CFG_SCK: U6.16 (ADBUS0); also elsewhere on the board
FT_ACBUS0: U6.26 (ACBUS0); also elsewhere on the board
FT_ACBUS1: U6.27 (ACBUS1); also elsewhere on the board
FT_ACBUS2: U6.28 (ACBUS2); also elsewhere on the board
FT_ACBUS3: U6.29 (ACBUS3); also elsewhere on the board
FT_D0: U6.38 (BDBUS0); also elsewhere on the board
FT_D1: U6.39 (BDBUS1); also elsewhere on the board
FT_D2: U6.40 (BDBUS2); also elsewhere on the board
FT_D3: U6.41 (BDBUS3); also elsewhere on the board
FT_D4: U6.43 (BDBUS4); also elsewhere on the board
FT_D5: U6.44 (BDBUS5); also elsewhere on the board
FT_D6: U6.45 (BDBUS6); also elsewhere on the board
FT_D7: U6.46 (BDBUS7); also elsewhere on the board
FT_PWREN_N: R17.2, U6.60 (~PWREN); also elsewhere on the board
FT_RD_N: U6.53 (BCBUS2); also elsewhere on the board
FT_RXF_N: U6.48 (BCBUS0); also elsewhere on the board
FT_SIWU_N: R18.2, U6.55 (BCBUS4); also elsewhere on the board
FT_SUSPEND_N: U6.36 (~SUSPEND); also elsewhere on the board
FT_TXE_N: U6.52 (BCBUS1); also elsewhere on the board
FT_WR_N: U6.54 (BCBUS3); also elsewhere on the board
GND: C15.2, C16.2, C17.2, C18.2, C19.2, C20.2, C21.2, C22.2, C23.2, C24.2, C25.2, C26.2, C27.2, C28.2, C29.2, C30.2, C31.2, J1.4 (GND), R10.2, R11.2, U5.2 (GND), U6.1 (GND), U6.5 (GND), U6.10 (AGND), U6.11 (GND), U6.13 (TEST), U6.15 (GND), U6.25 (GND), U6.35 (GND), U6.47 (GND), U6.51 (GND), U7.5 (GND), Y1.2 (G), Y1.4 (G); also elsewhere on the board
VBUS: J1.1 (VBUS), U5.5 (VBUS); also elsewhere on the board
